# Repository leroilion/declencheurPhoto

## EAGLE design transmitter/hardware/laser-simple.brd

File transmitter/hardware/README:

The hardware is very simple :
* An ATtiny2313 with crystal at 20MHz
* 2 2N1177 NPN transistor in darlington to control 5 LED
* ISP programming port
* Alimentation direct in 3V with 2 battery (without protection so be carreful)

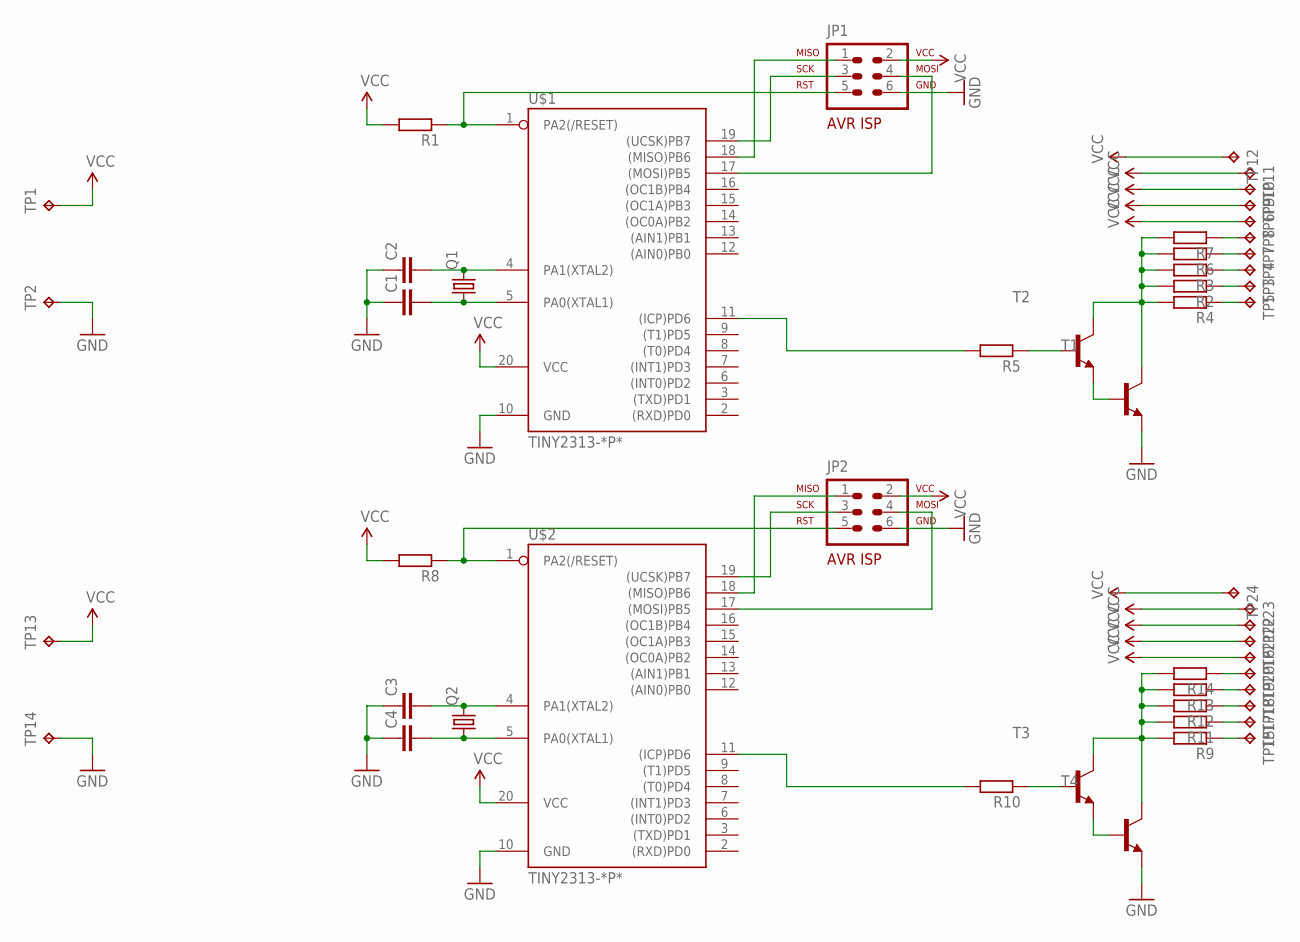
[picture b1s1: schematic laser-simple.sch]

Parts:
C1, C2, C3, C4: C-EU050-024X044; C050-024X044
JP1, JP2: AVR-ISP-6VERT; AVR-ISP-6
Q1, Q2: CRYSTALHC49U-V; HC49U-V
R1, R2, R3, R4, R5, R6, R7, R8, R9, R10, R11, R12, R13, R14: R-EU_0207/10; 0207/10
T1, T2, T3, T4: 2N1711-NPN-TO39-EBC; TO39
TP1, TP2, TP3, TP4, TP5, TP6, TP7, TP8, TP9, TP10, TP11, TP12, TP13, TP14, TP15, TP16, TP17, TP18, TP19, TP20, TP21, TP22, TP23, TP24: TPPAD1-13Y; P1-13Y
U$1, U$2: TINY2313-*P*; DIL20

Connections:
GND: C1.1, C2.1, C3.1, C4.1, JP1.6, JP2.6, T1.1 (E), T4.1 (E), TP2.TP, TP14.TP, U$1.10 (GND), U$2.10 (GND)
unnamed: C2.2, Q1.2, U$1.4 (PA1(XTAL2))
unnamed: C1.2, Q1.1, U$1.5 (PA0(XTAL1))
unnamed: JP1.5, R1.1, U$1.1 (PA2(/RESET))
unnamed: JP1.1, U$1.18 ((MISO)PB6)
unnamed: JP1.3, U$1.19 ((UCSK)PB7)
unnamed: JP1.4, U$1.17 ((MOSI)PB5)
unnamed: T1.2 (B), T2.1 (E)
unnamed: R2.2, R3.2, R4.2, R6.2, R7.2, T1.3 (C), T2.3 (C)
unnamed: R4.1, TP5.TP
unnamed: R6.1, TP7.TP
unnamed: R3.1, TP4.TP
unnamed: R2.1, TP3.TP
unnamed: C3.2, Q2.2, U$2.4 (PA1(XTAL2))
unnamed: R7.1, TP8.TP
unnamed: C4.2, Q2.1, U$2.5 (PA0(XTAL1))
unnamed: R5.1, T2.2 (B)
unnamed: JP2.5, R8.1, U$2.1 (PA2(/RESET))
unnamed: JP2.1, U$2.18 ((MISO)PB6)
unnamed: JP2.3, U$2.19 ((UCSK)PB7)
unnamed: JP2.4, U$2.17 ((MOSI)PB5)
unnamed: R5.2, U$1.11 ((ICP)PD6)
unnamed: R9.1, TP15.TP
unnamed: R10.1, T3.2 (B)
unnamed: R10.2, U$2.11 ((ICP)PD6)
unnamed: T3.1 (E), T4.2 (B)
unnamed: R9.2, R11.2, R12.2, R13.2, R14.2, T3.3 (C), T4.3 (C)
unnamed: R13.1, TP19.TP
unnamed: R12.1, TP18.TP
unnamed: R11.1, TP17.TP
unnamed: R14.1, TP20.TP
VCC: JP1.2, JP2.2, R1.2, R8.2, TP1.TP, TP6.TP, TP9.TP, TP10.TP, TP11.TP, TP12.TP, TP13.TP, TP16.TP, TP21.TP, TP22.TP, TP23.TP, TP24.TP, U$1.20 (VCC), U$2.20 (VCC)

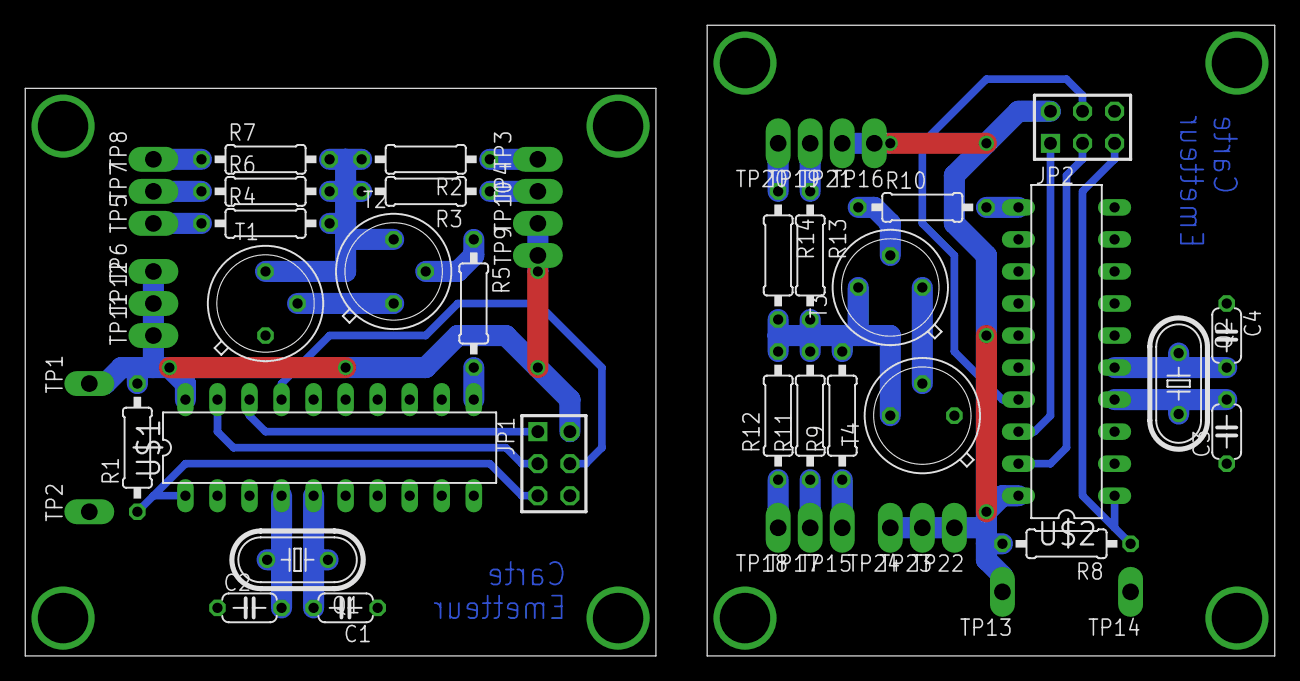
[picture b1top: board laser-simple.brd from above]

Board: 2 copper layers, 99.1 x 50.0 mm, 52 parts (0 on the bottom side), 32 nets.

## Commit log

2015-05-27 Add gitignore
2015-05-27 Add software for transimitter : It's a simple blink
2015-05-27 Add README to explain the program of transmitter
2015-05-27 Add Hardware schematic and board of transmitter
2015-05-27 Add solidwork version of box
2015-05-27 Add STL version of box
2015-05-27 Add core for arduino due
2015-05-27 Add gitignore to compile receiver program
2015-05-27 Add MAkefile to compile program for arduino due
2015-05-27 Add main.ino with blink program just for test
2015-05-27 Add README
2015-05-27 Add Timer libraries for Arduino due
2015-05-27 Add file to compute TFD
2015-05-27 Add sinus and cosinus table for my example
2015-05-27 Update main file to detect with TFD frequency
2015-05-27 Add excel file to compute sinus and cosinus table
2015-06-04 Change Frequency from 1464 to 7031Hz
2015-06-04 Change main code of receiver to take picture

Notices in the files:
parts and their libraries:
SparkFun-Aesthetics: Licensing: Creative Commons ShareAlike 4.0 International - https://creativecommons.org/licenses/by-sa/4.0
